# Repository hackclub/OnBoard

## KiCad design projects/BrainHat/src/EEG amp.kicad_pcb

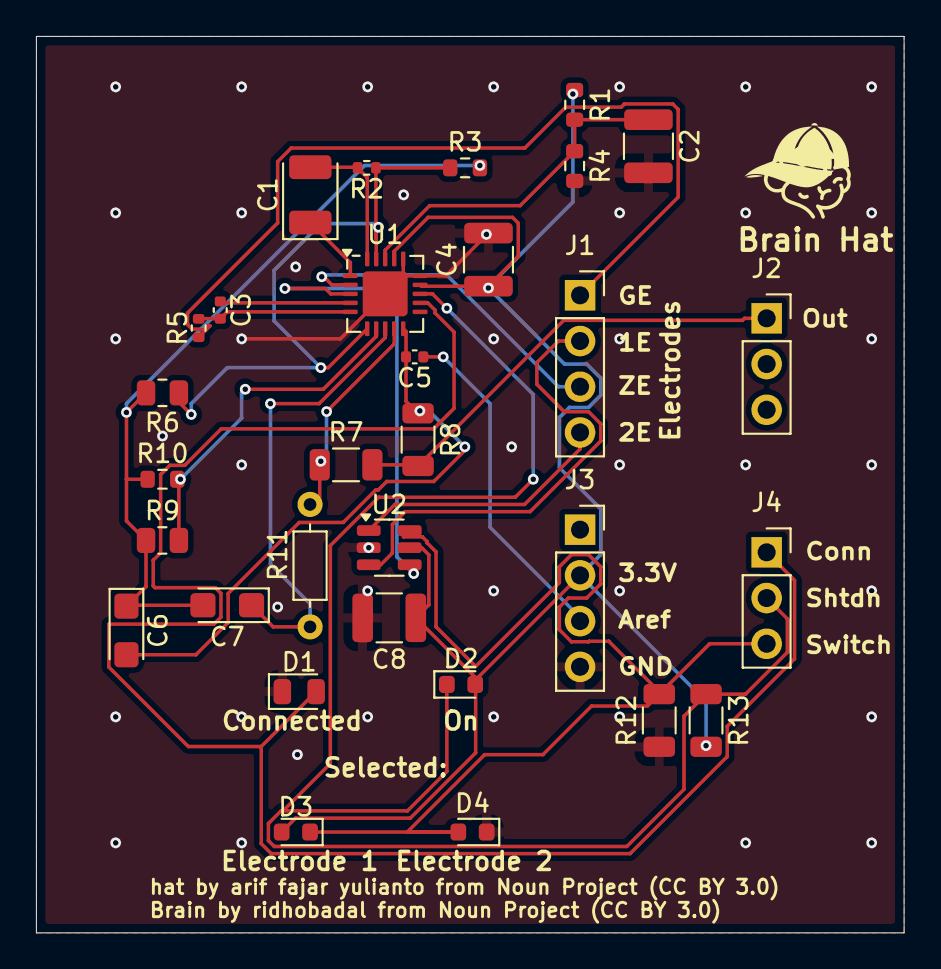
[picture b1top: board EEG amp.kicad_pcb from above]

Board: 2 copper layers, 48.2 x 49.8 mm, 31 parts (0 on the bottom side), 23 nets.

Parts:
C1: CA45-B6R3K107T; CP_EIA-3528-21_Kemet-B
C2, C4, C8: ECHU1C104GX5; C_1210_3225Metric
C3: CC0402JRX7R9BB102; C_0402_1005Metric
C5: 0402CG140J500NT; C_0402_1005Metric
C6, C7: CA45-A010K106T; CP_EIA-3216-12_Kemet-S
D1: XL-2012UWC; LED_0805_2012Metric
D2: XL-1608UBC-04; LED_0603_1608Metric
D3, D4: XL-1608UGC-04; LED_0603_1608Metric
J1: Electrodes; PinSocket_1x04_P2.54mm_Vertical
J2: Output; PinSocket_1x03_P2.54mm_Vertical
J3: Power; PinSocket_1x04_P2.54mm_Vertical
J4: Status; PinSocket_1x03_P2.54mm_Vertical
R1, R4: ARG03BTC1002; R_0603_1608Metric
R2, R5: SCR0402J330K; R_0402_1005Metric
R3, R10: 0603WAD3302T5E; R_0603_1608Metric
R6, R9: ARG05DTC1600; R_0805_2012Metric
R7, R8, R12, R13: 1206W4F1002T5E; R_1206_3216Metric
R11: CF1/6W-7.5KΩ±5%T52; R_Axial_DIN0207_L6.3mm_D2.5mm_P5.08mm_Horizontal
U1: AD8232; LFCSP-20-1EP_4x4mm_P0.5mm_EP2.5x2.5mm
U2: TS5A3159ADBVR; SOT-23-6

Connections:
1e: J1.2, U2.3
1o: J2.1, R7.2, R8.2
2e: J1.4, U2.1
+3.3V: C4.1, C8.1, D2.2 (A), D3.2 (A), J3.2, R1.1, R13.2, U1.14 (AC/~DC), U1.17 (Vss), U2.5 (V+)
Aref: C5.1, J3.3
GND: C2.2, C4.2, C8.2, D1.1 (K), D4.1 (K), J3.4, R4.2, R12.1, U1.15 (FR), U1.16 (GND), U1.21 (EP), U2.2 (GND)
Ge: J1.1, R5.1
HPDRIVE1: C1.1, U1.1 (HPDRIVE)
HPSENSE1: C1.2, R2.2, U1.20 (HPSENSE)
IAOUT1: R2.1, R3.1, R6.1, U1.6 (SW), U1.19 (IAOUT)
Ie: U1.3 (~IN), U2.4
unnamed: C6.1, C7.2, R3.2, R6.2, R9.1, R10.1
OPAMP+1: R9.2, R10.2, U1.7 (OPAMP+)
OPAMP-1: R7.1, R11.2, U1.9 (OPAMP-)
REFOUT1: C7.1, R11.1, U1.8 (REFOUT)
RLD1: C3.2, R5.2, U1.5 (RLD)
RLDFB1: C3.1, U1.4 (RLDFB)
UFOUT1: C5.2, C6.2, R8.1, U1.10 (OUT)
Vref: C2.1, R1.2, R4.1, U1.18 (REFIN)
Ze: J1.3, U1.2 (IN)
connected1: D1.2 (A), J4.1, U1.12 (LOD+)
shutdown: D2.1 (K), J4.2, R13.1, U1.13 (~SDN)
switch: D3.1 (K), D4.2 (A), J4.3, R12.2, U2.6

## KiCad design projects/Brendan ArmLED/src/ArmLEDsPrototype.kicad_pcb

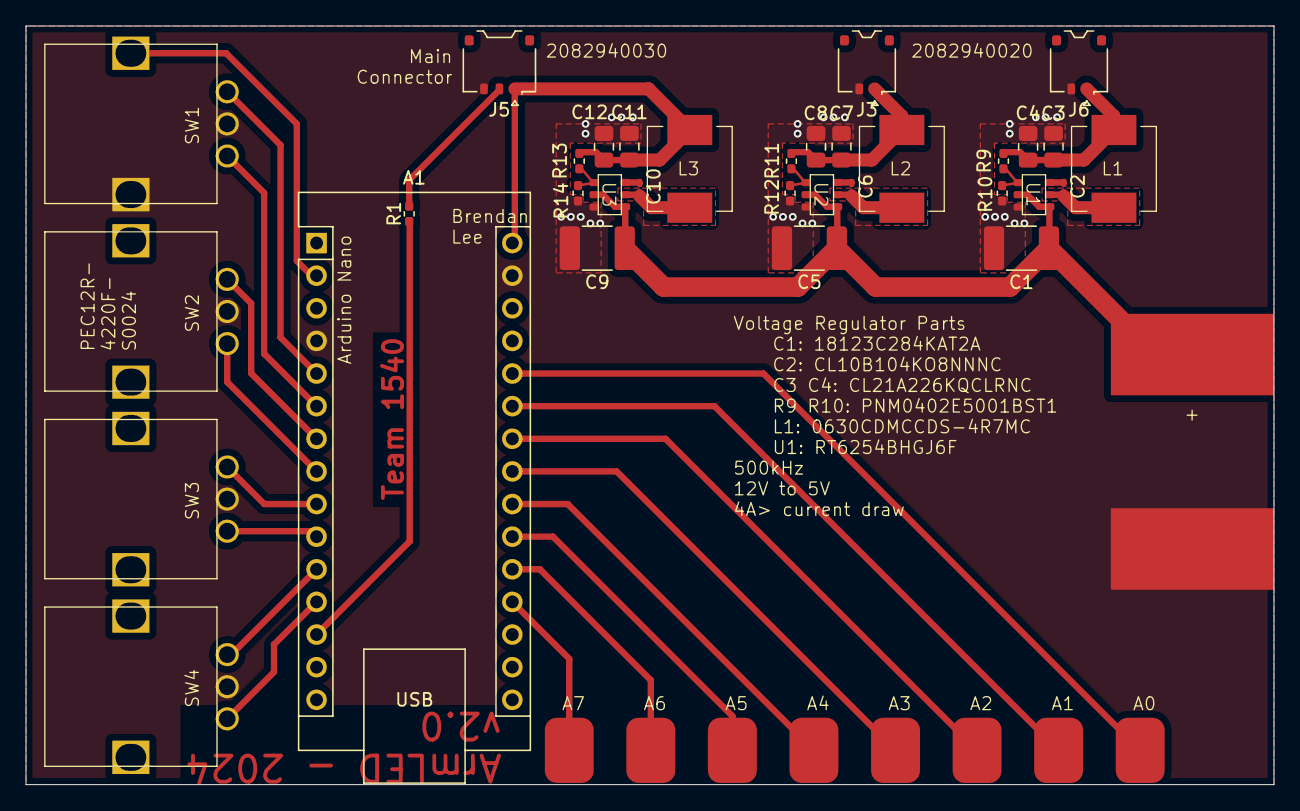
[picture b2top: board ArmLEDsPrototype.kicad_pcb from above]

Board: 2 copper layers, 97.2 x 59.1 mm, 35 parts (0 on the bottom side), 33 nets.

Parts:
A1: Arduino_Nano_Every; Arduino_Nano
BT1: Battery; BatteryPaddery
C1, C5, C9: C; C_1812_4532Metric_Pad1.57x3.40mm_HandSolder
C2, C6, C10: C; C_0201_0603Metric_Pad0.64x0.40mm_HandSolder
C3, C4, C7, C8, C11, C12: C; C_0805_2012Metric_Pad1.18x1.45mm_HandSolder
J1: Conn_01x08; 8Pad
J3, J6: Conn_01x02; Molex_Pico-EZmate_78171-0002_1x02-1MP_P1.20mm_Vertical
J5: Conn_01x03; Molex_Pico-EZmate_78171-0003_1x03-1MP_P1.20mm_Vertical
L1, L2, L3: L; 4r7007
R1, R9, R10, R11, R12, R13, R14: R; R_0402_1005Metric_Pad0.72x0.64mm_HandSolder
SW1: RotaryEncoder_Switch; RotaryEncoder
SW2, SW3, SW4: RotaryEncoder
U1, U2, U3: RT6254A

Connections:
+9V: BT1.1 (+), C1.1, C5.1, C9.1, U1.2 (EN), U1.4 (VIN), U2.2 (EN), U2.4 (VIN), U3.2 (EN), U3.4 (VIN)
/5V#1: C3.1, C4.1, J6.1, L1.2, R9.1
/5V#2: C7.1, C8.1, J3.1, L2.2, R11.1
/5V#3: A1.30 (VIN), C11.1, C12.1, J5.1, L3.2, R13.1
/Controller/Input1A: A1.6 (D3), SW1.A
/Controller/Input1B: A1.5 (D2), SW1.B
/Controller/Input2A: A1.8 (D5), SW2.A
/Controller/Input2B: A1.7 (D4), SW2.B
/Controller/Input3A: A1.10 (D7), SW3.A
/Controller/Input3B: A1.9 (D6), SW3.B
/Controller/Input4A: A1.12 (D9), SW4.A
/Controller/Input4B: A1.11 (D8), SW4.B
/Controller/InputS: A1.2 (RX1), SW1.S2
/LED_S: A1.13 (D10), R1.1
GND: A1.4 (GND), A1.29 (GND), BT1.2 (-), C1.2, C3.2, C4.2, C5.2, C7.2, C8.2, C9.2, C11.2, C12.2, J3.2, J5.3, J6.2, R10.2, R12.2, R14.2, SW1.C, SW1.S1, SW2.C, SW3.C, SW4.C, U1.3 (GND), U2.3 (GND), U3.3 (GND)
unnamed: A1.19 (A0), J1.1
unnamed: A1.20 (A1), J1.2
unnamed: A1.21 (A2), J1.3
unnamed: A1.22 (A3), J1.4
unnamed: A1.25 (A6), J1.7
unnamed: A1.26 (A7), J1.8
unnamed: A1.24 (SCL/A5), J1.6
unnamed: A1.23 (SDA/A4), J1.5
unnamed: J5.2, R1.2
unnamed: C2.1, U1.6 (BOOT)
unnamed: R9.2, R10.1, U1.1 (FB)
unnamed: C2.2, L1.1, U1.5 (LX)
unnamed: C6.1, U2.6 (BOOT)
unnamed: R11.2, R12.1, U2.1 (FB)
unnamed: C6.2, L2.1, U2.5 (LX)
unnamed: C10.1, U3.6 (BOOT)
unnamed: R13.2, R14.1, U3.1 (FB)
unnamed: C10.2, L3.1, U3.5 (LX)

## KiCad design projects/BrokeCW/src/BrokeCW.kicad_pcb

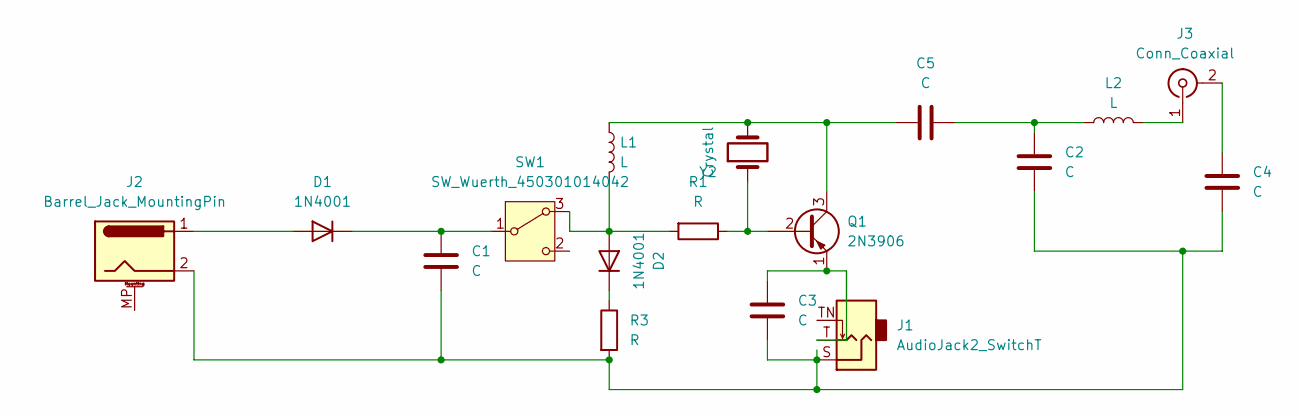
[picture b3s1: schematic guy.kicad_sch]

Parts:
C1, C2, C3, C4, C5: C; C_Rect_L4.0mm_W2.5mm_P2.50mm
D1, D2: 1N4001; D_DO-41_SOD81_P10.16mm_Horizontal
J1: AudioJack2_SwitchT; Jack_3.5mm_Lumberg_1503_07_Horizontal
J2: Barrel_Jack_MountingPin; BarrelJack_CLIFF_FC681465S_SMT_Horizontal
J3: Conn_Coaxial; BNC_Amphenol_B6252HB-NPP3G-50_Horizontal
L1, L2: L; L_Bourns-SRN6028
Q1: 2N3906; TO-92_Inline
R1, R3: R; R_Axial_DIN0207_L6.3mm_D2.5mm_P5.08mm_Vertical
SW1: SW_Wuerth_450301014042; SW_Slide-03_Wuerth-WS-SLTV_10x2.5x6.4_P2.54mm
Y2: Crystal; Crystal_HC49-U_Vertical

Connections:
unnamed: C1.2, C2.2, C3.2, C4.2, J1.S, J2.2, R3.2
unnamed: C2.1, C5.2, L2.1
unnamed: D1.2 (A), J2.1
unnamed: C1.1, D1.1 (K), SW1.1 (B)
unnamed: D2.2 (A), L1.2, R1.2, SW1.3 (A)
unnamed: D2.1 (K), R3.1
unnamed: C4.1, J3.2 (Ext)
unnamed: J3.1 (In), L2.2
unnamed: Q1.2 (B), R1.1, Y2.1
unnamed: C5.1, L1.1, Q1.3 (C), Y2.2
unnamed: C3.1, J1.T, Q1.1 (E)

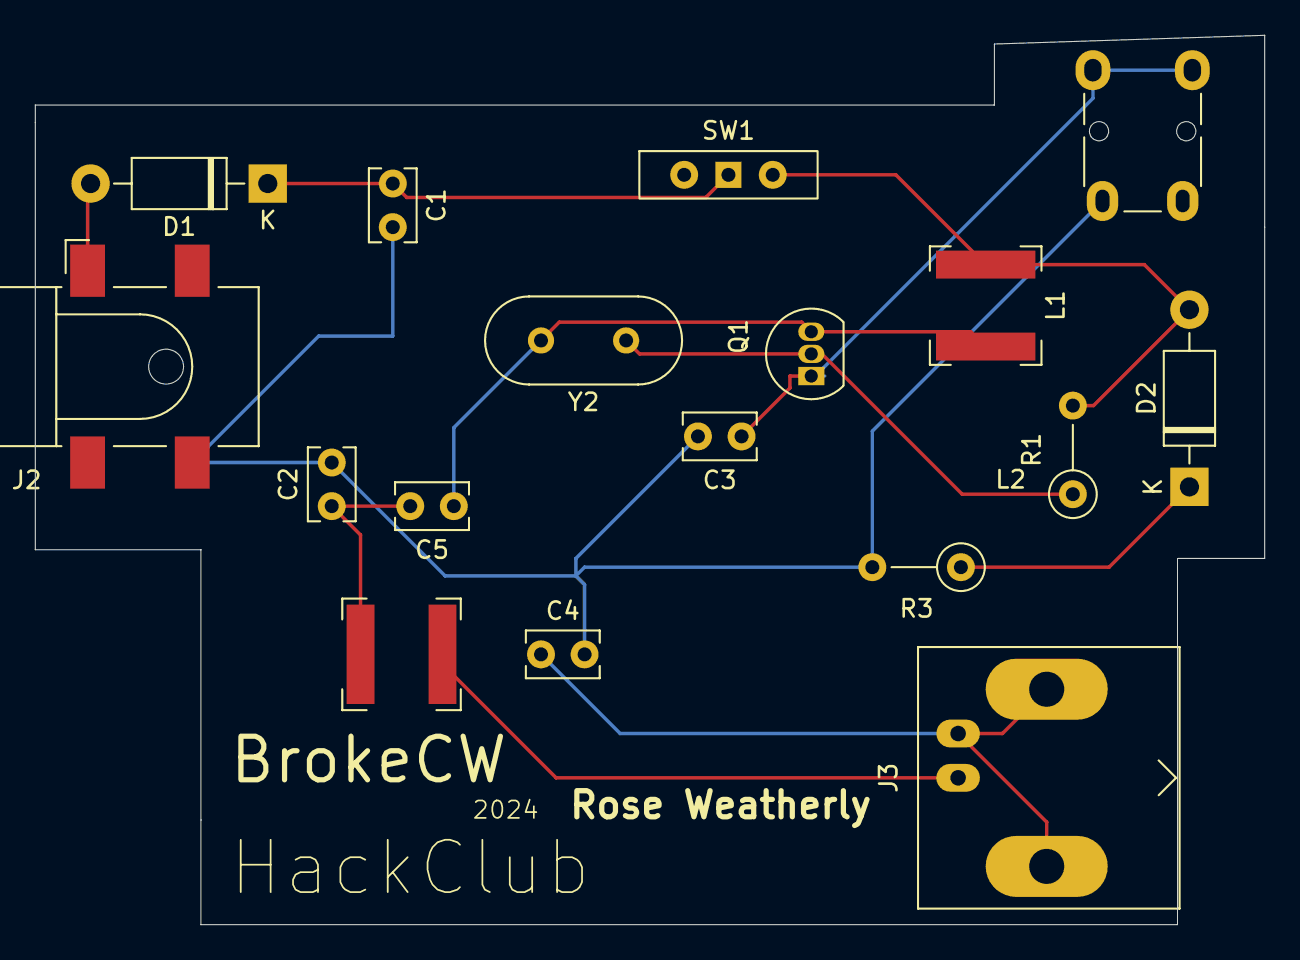
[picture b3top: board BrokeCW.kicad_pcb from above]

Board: 2 copper layers, 70.5 x 51.0 mm, 17 parts (0 on the bottom side), 11 nets.

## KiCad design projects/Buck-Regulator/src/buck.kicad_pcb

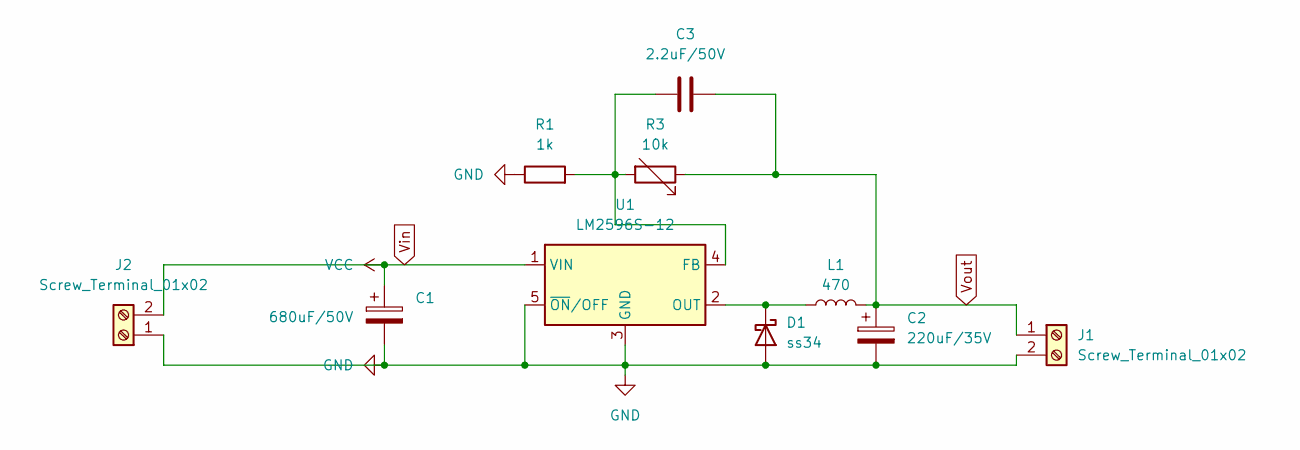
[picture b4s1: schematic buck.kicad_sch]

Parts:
C1: 680uF/50V; CAP-SMD_BD12.5-L13.0-W13.0-LS14.4-FD; LCSC C487372
C2: 220uF/35V; C_Elec_8x10.2; LCSC C242057
C3: 2.2uF/50V; C_0603_1608Metric
D1: ss34; D_SMA
J1, J2: Screw_Terminal_01x02; TerminalBlock_Phoenix_MKDS-1,5-2-5.08_1x02_P5.08mm_Horizont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; LCSC C709041
L1: 470; L_SXN_SMDRI127; LCSC C2929509
R1: 1k; R_1206_3216Metric
R3: 10k; Potentiometer_Bourns_3296W_Vertical; LCSC C118954
U1: LM2596S-12; TO-263-5_TabPin3; LCSC C5349986

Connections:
GND: C1.2, C2.2, D1.2 (A), J1.2, J2.1, R1.1, U1.3 (GND), U1.5 (~ON/OFF)
unnamed: D1.1 (K), L1.1, U1.2 (OUT)
unnamed: C3.1, R1.2, R3.2, U1.4 (FB)
Vin: C1.1, J2.2, U1.1 (VIN)
Vout: C2.1, C3.2, J1.1, L1.2, R3.1

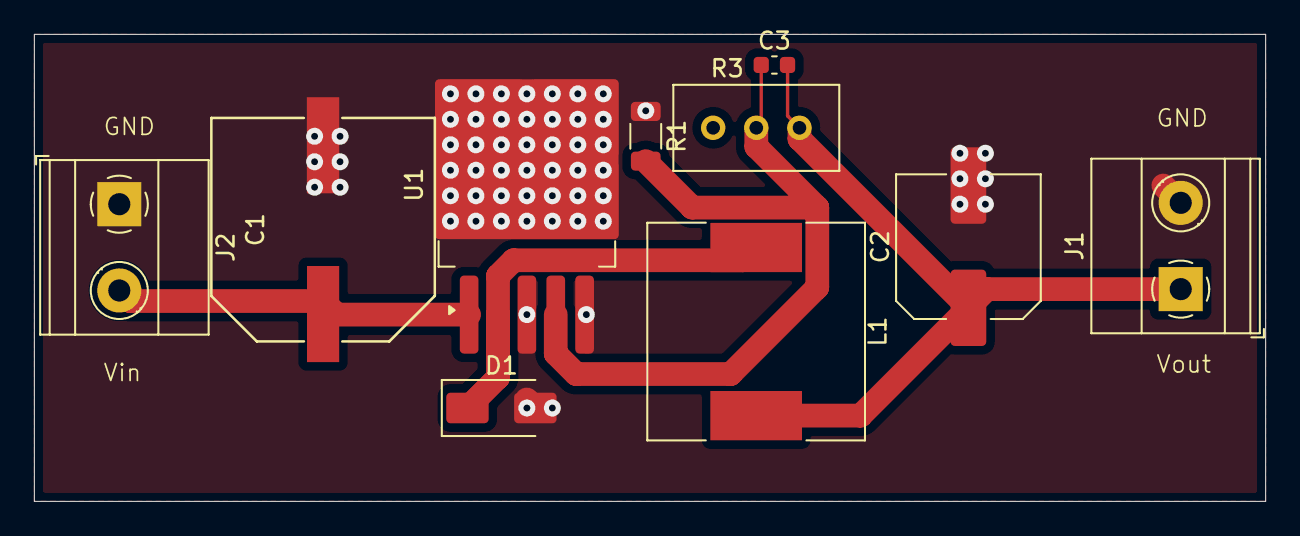
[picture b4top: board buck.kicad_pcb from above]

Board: 2 copper layers, 72.5 x 27.5 mm, 10 parts (0 on the bottom side), 5 nets.

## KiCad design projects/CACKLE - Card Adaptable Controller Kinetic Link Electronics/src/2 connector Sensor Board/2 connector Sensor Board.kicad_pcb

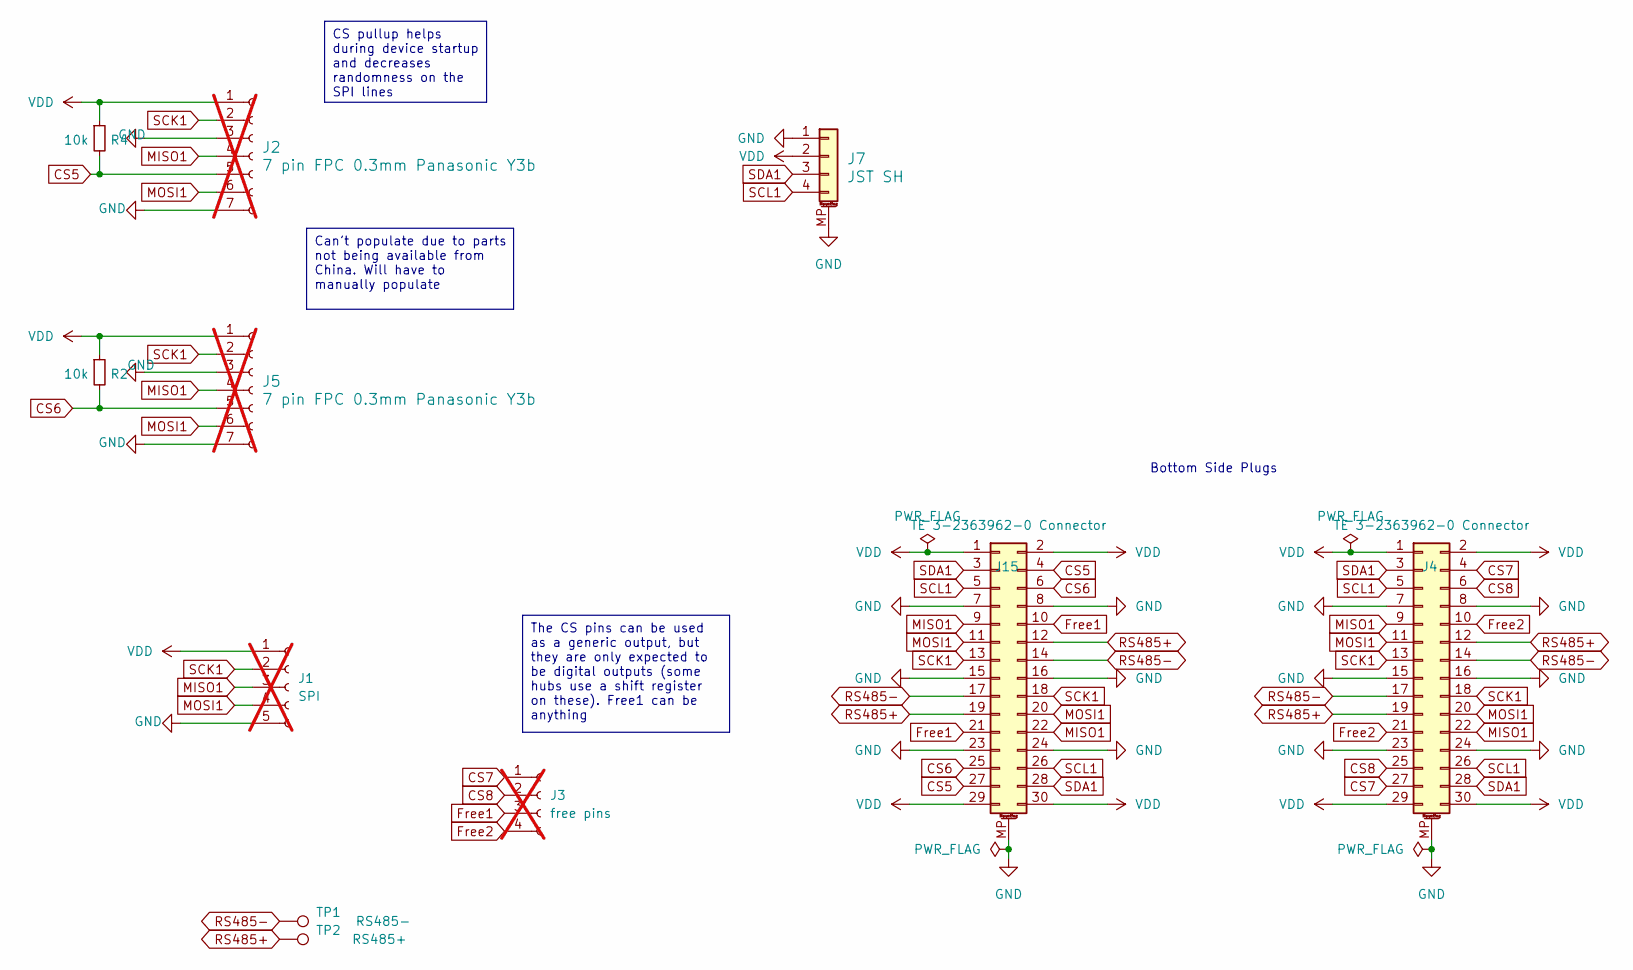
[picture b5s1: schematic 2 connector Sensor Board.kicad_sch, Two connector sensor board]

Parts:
J1: SPI; PinHeader_1x05_P1.27mm_Vertical; not fitted
J2, J5: 7 pin FPC 0.3mm Panasonic Y3b; fpc_7pin_0.3mm_connector Panasonic; not fitted
J3: free pins; PinHeader_1x04_P1.27mm_Vertical; not fitted
J4, J15: TE 3-2363962-0 Connector; TE_mezzanine_conn_3-2363962-0; LCSC C425104
J7: JST SH; JST_SH_SM04B-SRSS-TB_1x04-1MP_P1.00mm_Horizontal; LCSC C160404
R2, R4: 10k; R_0402_1005Metric; LCSC C25744
TP1: RS485-; TestPoint_Pad_D1.0mm
TP2: RS485+; TestPoint_Pad_D1.0mm

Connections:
CS5: J2.5, J15.4, J15.27, R4.2
CS6: J5.5, J15.6, J15.25, R2.2
CS7: J3.1, J4.4, J4.27
CS8: J3.2, J4.6, J4.25
Free1: J3.3, J15.10, J15.21
Free2: J3.4, J4.10, J4.21
GND: J1.5, J2.3, J2.7, J4.7, J4.8, J4.15, J4.16, J4.23, J4.24, J4.MP (MountPin), J5.3, J5.7, J7.1, J7.MP (MountPin), J15.7, J15.8, J15.15, J15.16, J15.23, J15.24, J15.MP (MountPin)
MISO1: J1.3, J2.4, J4.9, J4.22, J5.4, J15.9, J15.22
MOSI1: J1.4, J2.6, J4.11, J4.20, J5.6, J15.11, J15.20
RS485+: J4.12, J4.19, J15.12, J15.19, TP2.1
RS485-: J4.14, J4.17, J15.14, J15.17, TP1.1
SCK1: J1.2, J2.2, J4.13, J4.18, J5.2, J15.13, J15.18
SCL1: J4.5, J4.26, J7.4, J15.5, J15.26
SDA1: J4.3, J4.28, J7.3, J15.3, J15.28
VDD: J1.1, J2.1, J4.1, J4.2, J4.29, J4.30, J5.1, J7.2, J15.1, J15.2, J15.29, J15.30, R2.1, R4.1

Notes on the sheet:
Can't populate due to parts not being available from China. Will have to manually populate
CS pullup helps during device startup and decreases randomness on the SPI lines
The CS pins can be used as a generic output, but they are only expected to be digital outputs (some hubs use a shift register on these). Free1 can be anything
Bottom Side Plugs

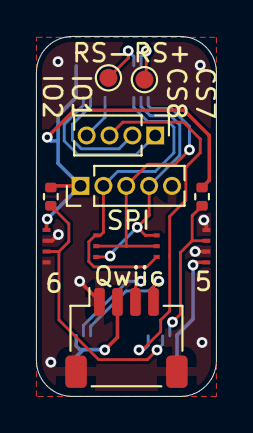
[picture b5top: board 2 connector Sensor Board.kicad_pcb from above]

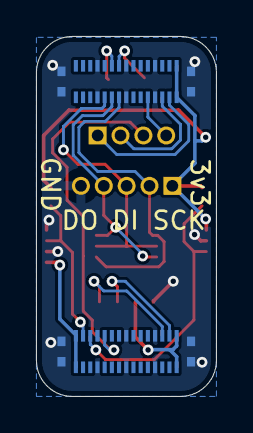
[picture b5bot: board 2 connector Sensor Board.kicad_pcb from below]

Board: 2 copper layers, 10.0 x 20.0 mm, 11 parts (2 on the bottom side), 15 nets.

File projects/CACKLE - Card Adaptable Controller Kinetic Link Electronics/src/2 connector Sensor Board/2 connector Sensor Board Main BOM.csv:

"Id";"Designator";"Footprint";"Quantity";"Designation";"Supplier and ref";
1;"J1";"PinHeader_1x05_P1.27mm_Vertical";1;"SPI";;;
2;"J7";"JST_SH_SM04B-SRSS-TB_1x04-1MP_P1.00mm_Horizontal";1;"JST SH";;;
3;"R2,R4";"R_0402_1005Metric";2;"10k";;;
4;"J3";"PinHeader_1x04_P1.27mm_Vertical";1;"free pins";;;
5;"J2,J5";"fpc_7pin_0.3mm_connector Panasonic";2;"7 pin FPC 0.3mm Panasonic Y3b";;;
6;"J4,J15";"TE_mezzanine_conn_3-2363962-0";2;"TE 3-2363962-0 Connector";;;

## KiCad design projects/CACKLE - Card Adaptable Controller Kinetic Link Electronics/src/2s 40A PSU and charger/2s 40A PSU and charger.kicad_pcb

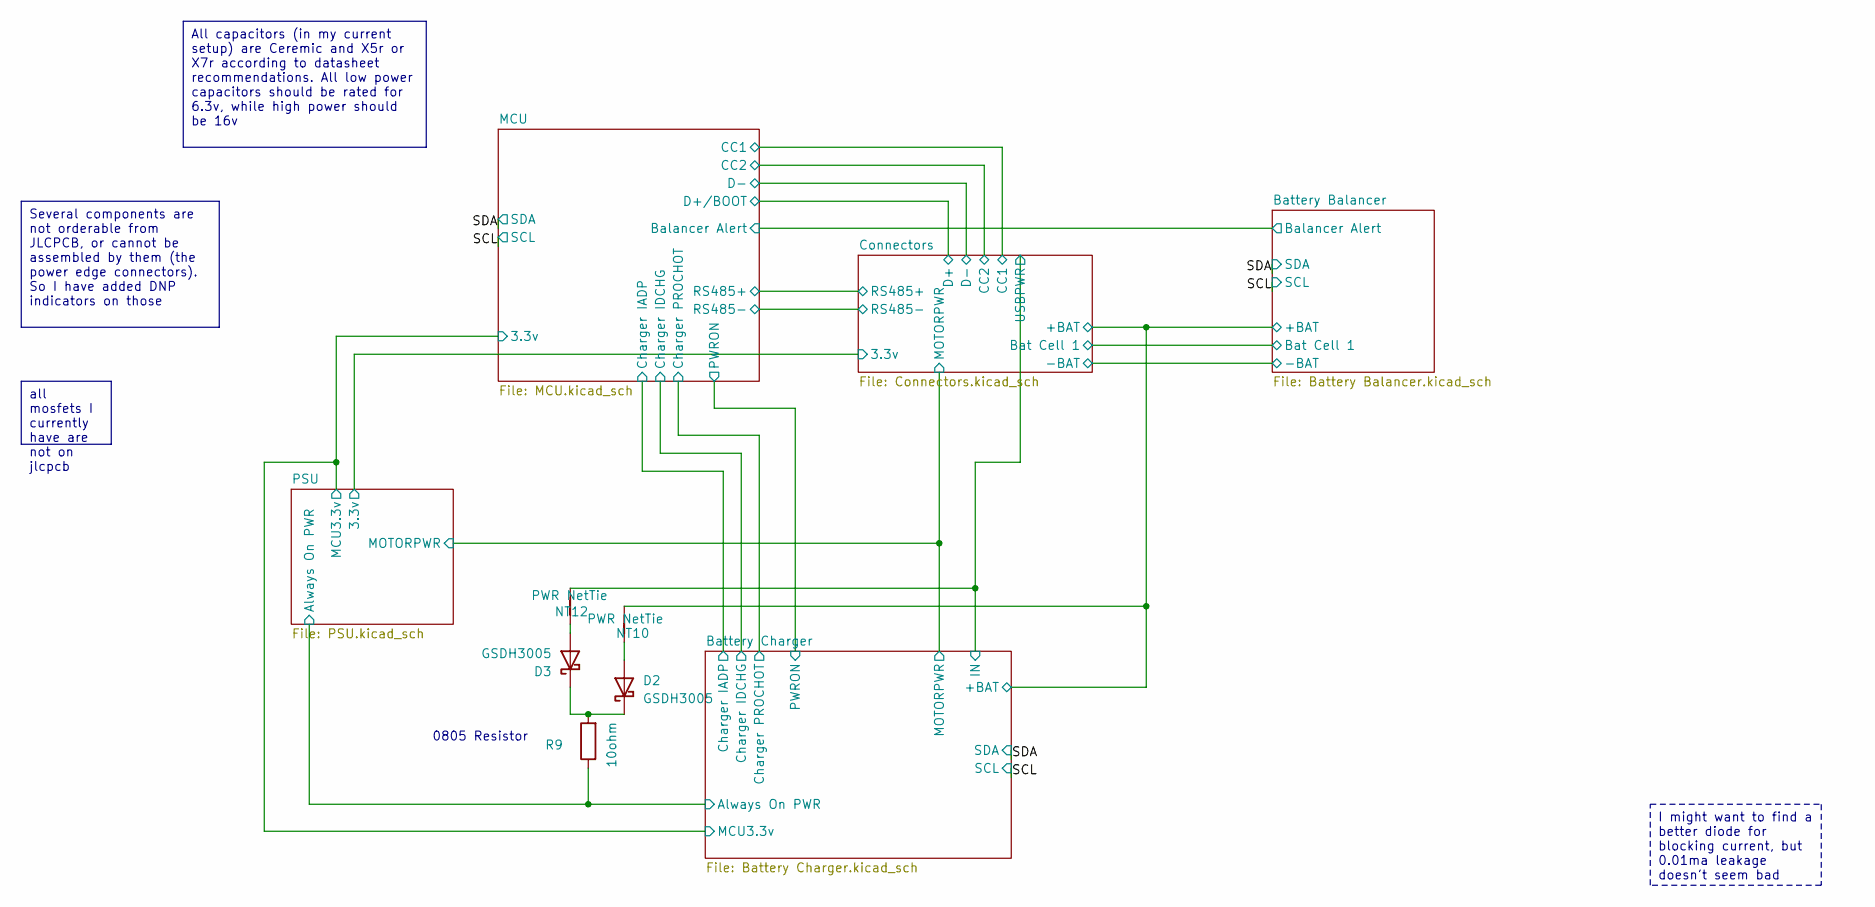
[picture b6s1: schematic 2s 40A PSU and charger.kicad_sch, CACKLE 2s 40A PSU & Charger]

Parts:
D2, D3: GSDH3005; D_0402_1005Metric; LCSC C2837790
NT10, NT12: PWR NetTie; NetTie-2_SMD_Pad0.28mm
R9: 10ohm; R_0805_2012Metric; LCSC C17415

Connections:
/Battery Balancer/+BAT: NT10.2; also elsewhere on the board
/Battery Charger/Always On PWR: R9.1; also elsewhere on the board
/Battery Charger/IN: NT12.2; also elsewhere on the board
unnamed: D2.2 (A), NT10.1
unnamed: D2.1 (K), D3.1 (K), R9.2
unnamed: D3.2 (A), NT12.1

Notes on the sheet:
All capacitors (in my current setup) are Ceremic and X5r or X7r according to datasheet recommendations. All low power capacitors should be rated for 6.3v, while high power should be 16v
Several components are not orderable from JLCPCB, or cannot be assembled by them (the power edge connectors). So I have added DNP indicators on those
all mosfets I currently have are not on jlcpcb
I might want to find a better diode for blocking current, but 0.01ma leakage doesn't seem bad
0805 Resistor

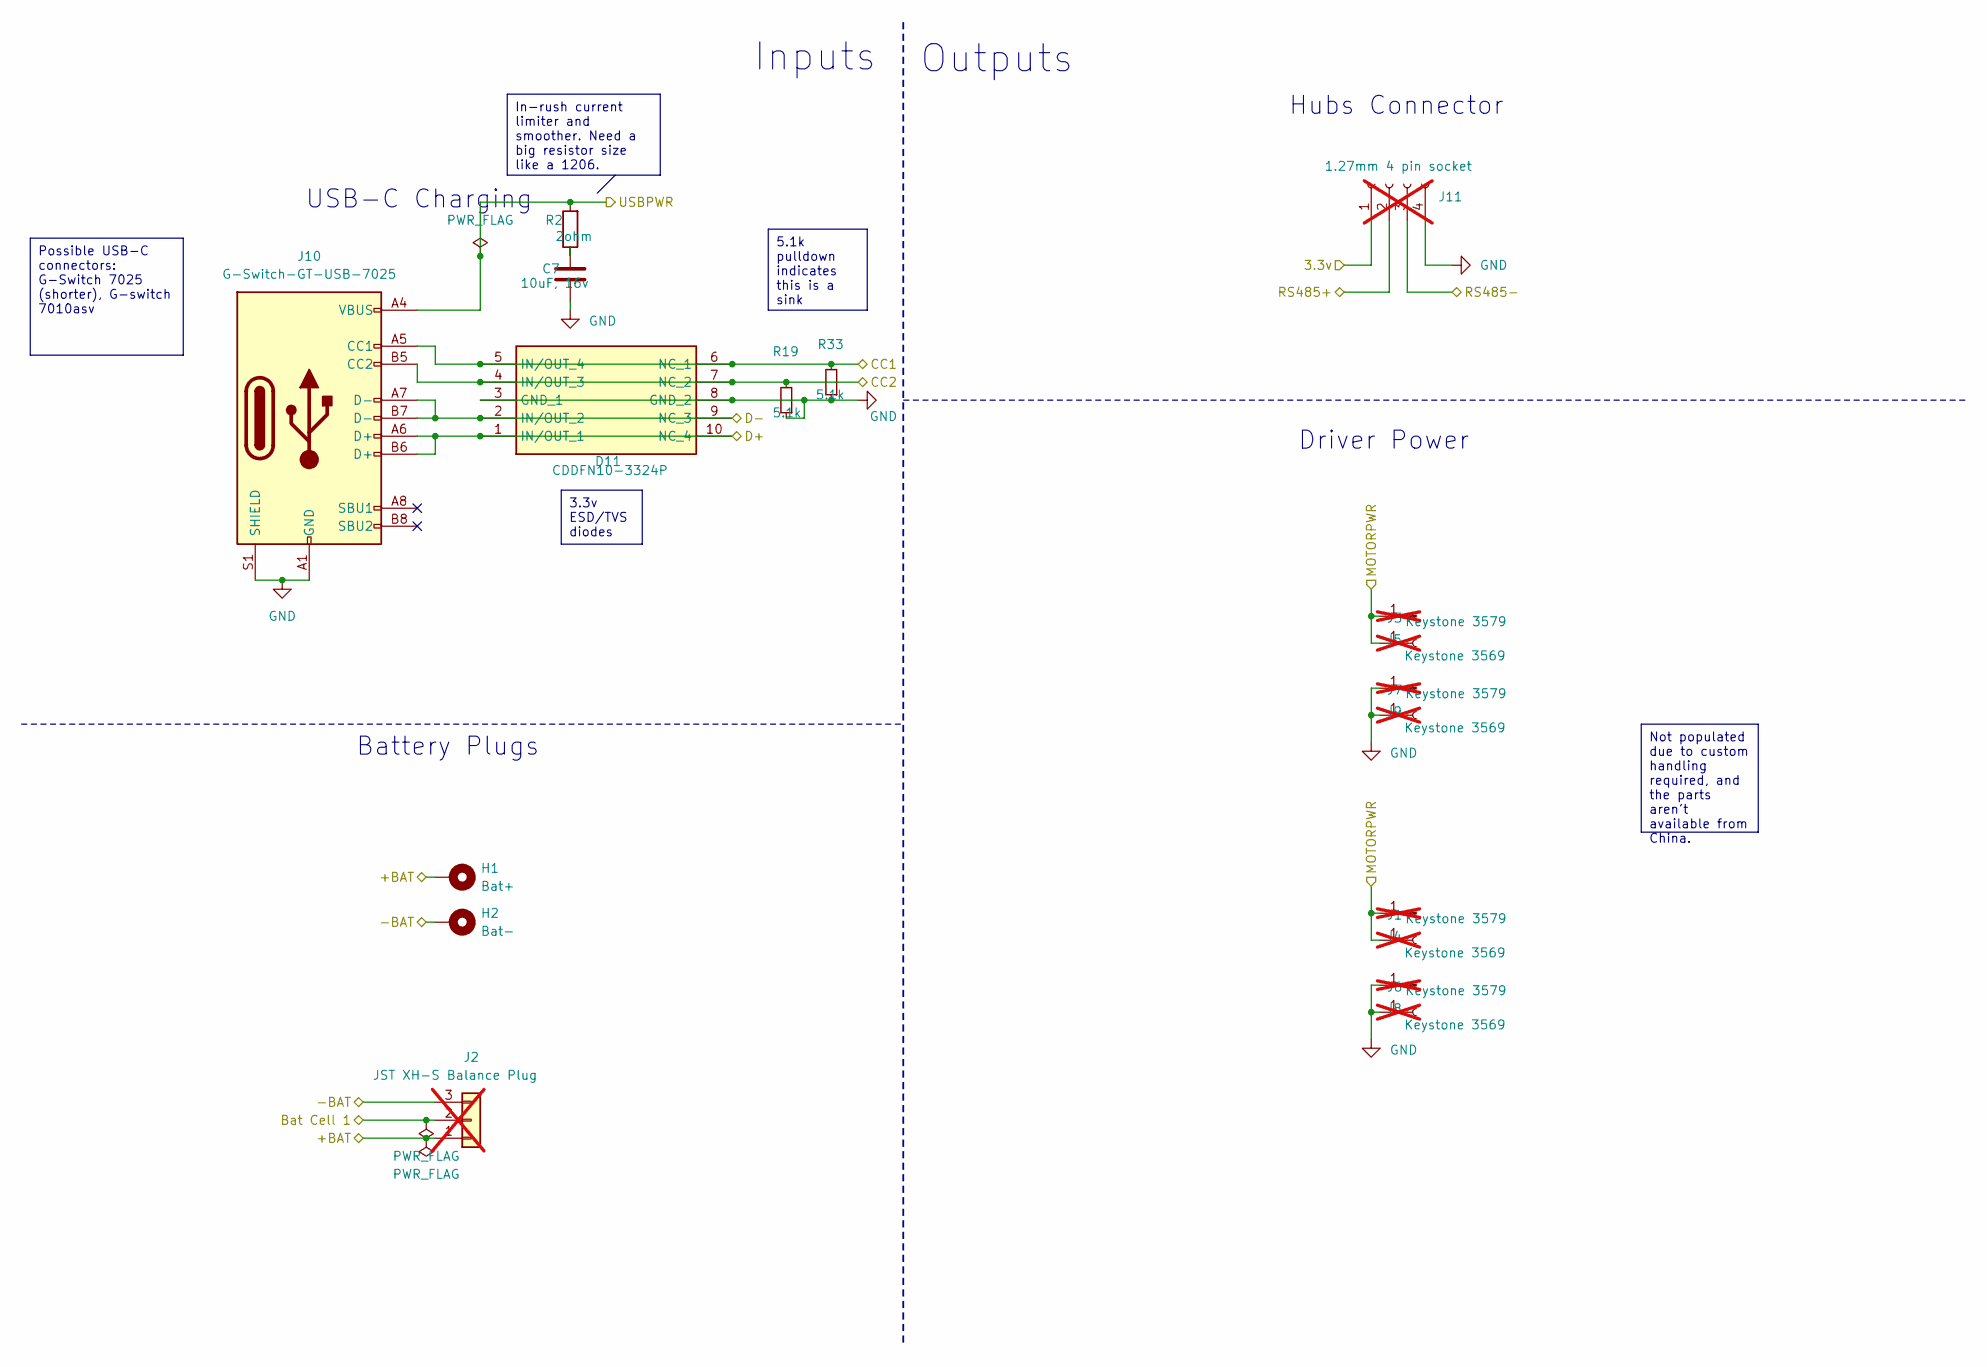
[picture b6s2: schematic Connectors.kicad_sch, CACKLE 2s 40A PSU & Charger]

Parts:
C7: 10uF, 16v; C_0805_2012Metric; LCSC C15850
D11: CDDFN10-3324P; CDDFN103324P; Mouser Part Number 652-CDDFN10-3324P
H1: Bat+; MountingHole_2.2mm_M2_Pad_Via
H2: Bat-; MountingHole_2.2mm_M2_Pad_Via
J1, J3, J6, J7: Keystone 3579; Keystone_3579; not fitted
J2: JST XH-S Balance Plug; JST_XH_S3B-XH-A_1x03_P2.50mm_Horizontal; LCSC C161860; not fitted
J4, J5, J8, J9: Keystone 3569; Keystone_3569_half; not fitted
J10: G-Switch-GT-USB-7025; USB_C_G-Switch_GT-USB-7025-JLCPCBv; LCSC C963213
J11: 1.27mm 4 pin socket; PinSocket_1x04_P1.27mm_Vertical; not fitted
R2: 2ohm; R_0805_2012Metric; LCSC C17521
R19, R33: 5.1k; R_0402_1005Metric; LCSC C25905

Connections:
/Battery Balancer/+BAT: H1.1, J2.1; also elsewhere on the board
/Battery Balancer/-BAT: H2.1, J2.3; also elsewhere on the board
/Battery Balancer/Bat Cell 1: J2.2; also elsewhere on the board
/Battery Charger/IN: J10.A4 (VBUS), J10.A9 (VBUS), J10.B4 (VBUS), J10.B9 (VBUS), R2.2; also elsewhere on the board
/Battery Charger/MOTORPWR: J1.1, J3.1, J4.1, J5.1; also elsewhere on the board
/Connectors/3.3v: J11.1; also elsewhere on the board
/Connectors/CC1: D11.5 (IN/OUT_4), D11.6 (NC_1), J10.A5 (CC1), R33.2; also elsewhere on the board
/Connectors/CC2: D11.4 (IN/OUT_3), D11.7 (NC_2), J10.B5 (CC2), R19.2; also elsewhere on the board
/Connectors/D+: D11.1 (IN/OUT_1), D11.10 (NC_4), J10.A6 (D+), J10.B6 (D+); also elsewhere on the board
/Connectors/D-: D11.2 (IN/OUT_2), D11.9 (NC_3), J10.A7 (D-), J10.B7 (D-); also elsewhere on the board
/Connectors/RS485+: J11.2; also elsewhere on the board
/Connectors/RS485-: J11.3; also elsewhere on the board
GND: C7.2, D11.3 (GND_1), D11.8 (GND_2), J6.1, J7.1, J8.1, J9.1, J10.A1 (GND), J10.A12 (GND), J10.B1 (GND), J10.B12 (GND), J10.GND, J10.S1 (SHIELD), J11.4, R19.1, R33.1; also elsewhere on the board
unnamed: C7.1, R2.1

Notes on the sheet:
In-rush current limiter and smoother. Need a big resistor size like a 1206.
5.1k pulldown indicates this is a sink
Possible USB-C connectors: G-Switch 7025 (shorter), G-switch 7010asv
3.3v ESD/TVS diodes
Not populated due to custom handling required, and the parts aren't available from China.
Outputs
USB-C Charging
Inputs
Driver Power
Hubs Connector
Battery Plugs

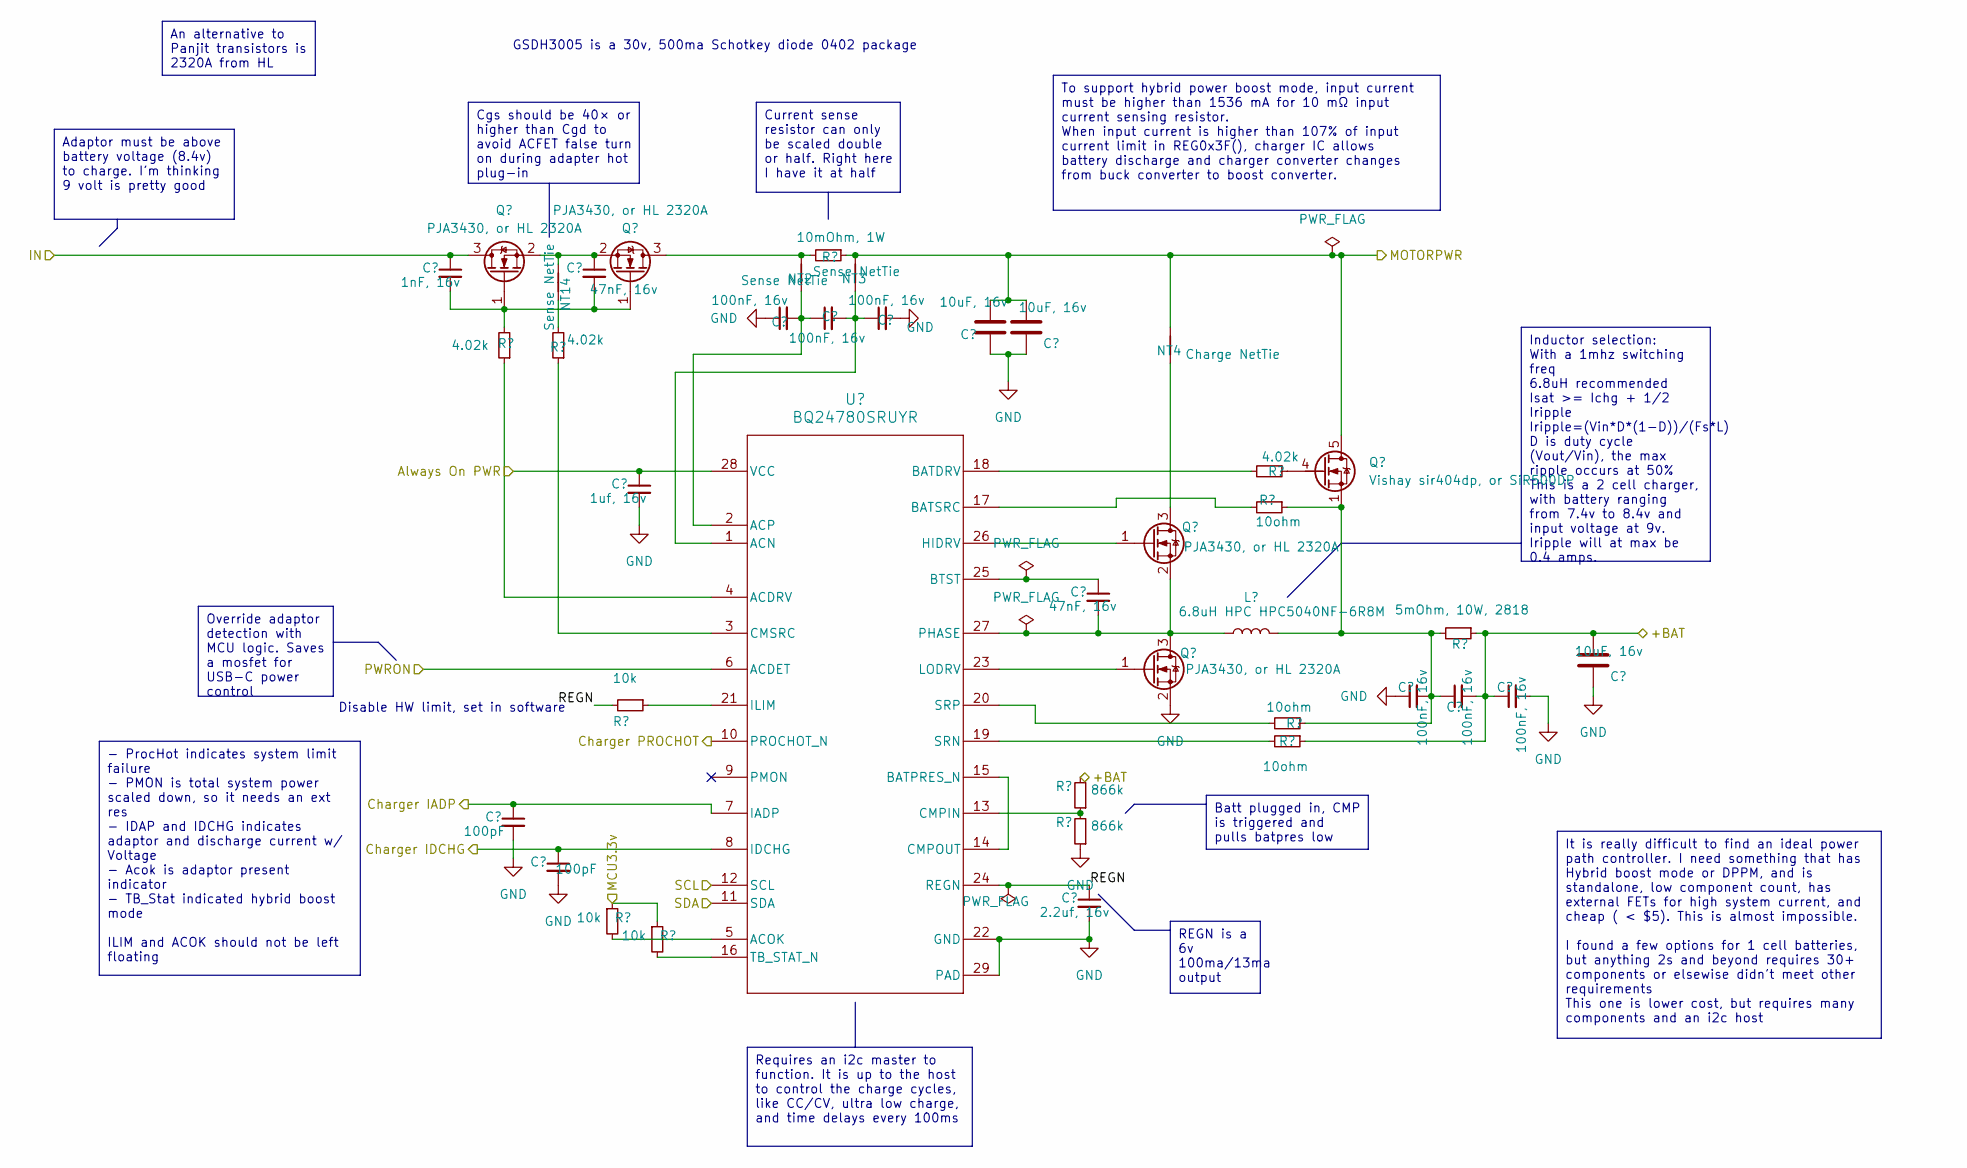
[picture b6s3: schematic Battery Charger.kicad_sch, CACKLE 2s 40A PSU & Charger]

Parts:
C5: 1nF, 16v; C_0402_1005Metric
C6, C17: 47nF, 16v; C_0603_1608Metric
C9, C10, C11, C21, C22, C23: 100nF, 16v; C_0402_1005Metric
C12, C14, C20: 10uF, 16v; C_0805_2012Metric
C15: 1uf, 16v; C_0402_1005Metric
C24: 2.2uf, 16v; C_0603_1608Metric
C29, C30: 100pF; C_0402_1005Metric
L2: 6.8uH HPC HPC5040NF-6R8M; L_Bourns_SDR0604
NT2, NT3, NT14: Sense NetTie; NetTie-2_SMD_Pad0.2mm
NT4: Charge NetTie; NetTie-2_SMD_Pad0.8mm
Q1, Q2, Q4, Q5: PJA3430, or HL 2320A; SC-59
Q3: Vishay sir404dp, or SiR500DP; PQFN-8-EP_6x5mm_P1.27mm_Generic; LCSC C3289487
R1: 10mOhm, 1W; R_1206_3216Metric
R7, R8, R10: 4.02k; R_0402_1005Metric
R12, R21, R22: 10ohm; R_0402_1005Metric
R18: 5mOhm, 10W, 2818; R_Vishay_2818
R20, R23, R24: 10k; R_0402_1005Metric
R30, R31: 866k; R_0402_1005Metric
U3: BQ24780SRUYR; RUY0028A

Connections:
/Battery Balancer/+BAT: C20.2, C22.2, C23.1, R18.1, R22.1, R30.2; also elsewhere on the board
/Battery Charger/Always On PWR: C15.1, U3.28 (VCC); also elsewhere on the board
/Battery Charger/Charger IADP: C29.1, U3.7 (IADP); also elsewhere on the board
/Battery Charger/Charger IDCHG: C30.1, U3.8 (IDCHG); also elsewhere on the board
/Battery Charger/Charger PROCHOT: U3.10 (PROCHOT_N); also elsewhere on the board
/Battery Charger/IN: C5.1, Q1.3 (D); also elsewhere on the board
/Battery Charger/MCU3.3v: R23.1, R24.1; also elsewhere on the board
/Battery Charger/MOTORPWR: C12.2, C14.2, NT3.2, NT4.2, Q3.5 (D), Q3.6 (D), Q3.7 (D), Q3.8 (D), R1.1; also elsewhere on the board
/Battery Charger/PWRON: U3.6 (ACDET); also elsewhere on the board
/Battery Charger/REGN: C24.1, R20.2, U3.24 (REGN)
/SCL: U3.12 (SCL); also elsewhere on the board
/SDA: U3.11 (SDA); also elsewhere on the board
GND: C9.1, C11.2, C12.1, C14.1, C15.2, C20.1, C21.1, C23.2, C24.2, C29.2, C30.2, Q5.2 (S), R31.1, U3.22 (GND), U3.29 (PAD); also elsewhere on the board
unnamed: C21.2, C22.1, L2.2, Q3.1 (S), Q3.2 (S), Q3.3 (S), R12.1, R18.2, R21.1
unnamed: NT14.1, R7.2
unnamed: C5.2, C6.2, Q1.1 (G), Q2.1 (G), R8.2
unnamed: C6.1, NT14.2, Q1.2 (S), Q2.2 (S)
unnamed: NT2.2, Q2.3 (D), R1.2
unnamed: Q3.4 (G), R10.1
unnamed: NT4.1, Q4.3 (D)
unnamed: Q4.1 (G), U3.26 (HIDRV)
unnamed: C17.2, L2.1, Q4.2 (S), Q5.3 (D), U3.27 (PHASE)
unnamed: Q5.1 (G), U3.23 (LODRV)
unnamed: R8.1, U3.4 (ACDRV)
unnamed: C10.2, C11.1, NT3.1, U3.1 (ACN)
unnamed: R23.2, U3.5 (ACOK)
unnamed: C9.2, C10.1, NT2.1, U3.2 (ACP)
unnamed: R10.2, U3.18 (BATDRV)
unnamed: U3.14 (CMPOUT), U3.15 (BATPRES_N)
unnamed: R12.2, U3.17 (BATSRC)
unnamed: C17.1, U3.25 (BTST)
unnamed: R30.1, R31.2, U3.13 (CMPIN)
unnamed: R7.1, U3.3 (CMSRC)
unnamed: R20.1, U3.21 (ILIM)
unnamed: R22.2, U3.19 (SRN)
unnamed: R21.2, U3.20 (SRP)
unnamed: R24.2, U3.16 (TB_STAT_N)

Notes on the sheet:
To support hybrid power boost mode, input current must be higher than 1536 mA for 10 mΩ input current sensing resistor. When input current is higher than 107% of input current limit in REG0x3F(), charger IC allows battery discharge and charger converter changes from buck converter to boost converte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
Batt plugged in, CMP is triggered and pulls batpres low
Inductor selection: With a 1mhz switching freq 6.8uH recommended Isat >= Ichg + 1/2 Iripple Iripple=(Vin*D*(1-D))/(Fs*L) D is duty cycle (Vout/Vin), the max ripple occurs at 50% This is a 2 cell charger, with battery ranging from 7.4v to 8.4v and input voltage at 9v. Iripple will at max be 0.4 amps.
It is really difficult to find an ideal power path controller. I need something that has Hybrid boost mode or DPPM, and is standalone, low component count, has external FETs for high system current, and cheap ( < $5). This is almost impossible. I found a few options for 1 cell batteries, but anythi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
Requires an i2c master to function. It is up to the host to control the charge cycles, like CC/CV, ultra low charge, and time delays every 100ms
Cgs should be 40× or higher than Cgd to avoid ACFET false turn on during adapter hot plug-in
Current sense resistor can only be scaled double or half. Right here I have it at half
Override adaptor detection with MCU logic. Saves a mosfet for USB-C power control
Adaptor must be above battery voltage (8.4v) to charge. I'm thinking 9 volt is pretty good
REGN is a 6v 100ma/13ma output
An alternative to Panjit transistors is 2320A from HL
- ProcHot indicates system limit failure - PMON is total system power scaled down, so it needs an ext res - IDAP and IDCHG indicates adaptor and discharge current w/ Voltage - Acok is adaptor present indicator - TB_Stat indicated hybrid boost mode ILIM and ACOK should not be left floating
GSDH3005 is a 30v, 500ma Schotkey diode 0402 package
Disable HW limit, set in software

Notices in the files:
projects/BrainHat/src/EEG amp.kicad_pcb:
hat by arif fajar yulianto from Noun Project (CC BY 3.0)
Brain by ridhobadal from Noun Project (CC BY 3.0)
projects/CACKLE - Card Adaptable Controller Kinetic Link Electronics/src/2s 40A PSU and charger/2s 40A PSU and charger.kicad_pcb:
©2024
projects/CACKLE - Card Adaptable Controller Kinetic Link Electronics/src/DRV8213 brushed Motor Driver/DRV8213 brushed Motor Driver.kicad_pcb:
Licensed under CERN-OHL-S V2
